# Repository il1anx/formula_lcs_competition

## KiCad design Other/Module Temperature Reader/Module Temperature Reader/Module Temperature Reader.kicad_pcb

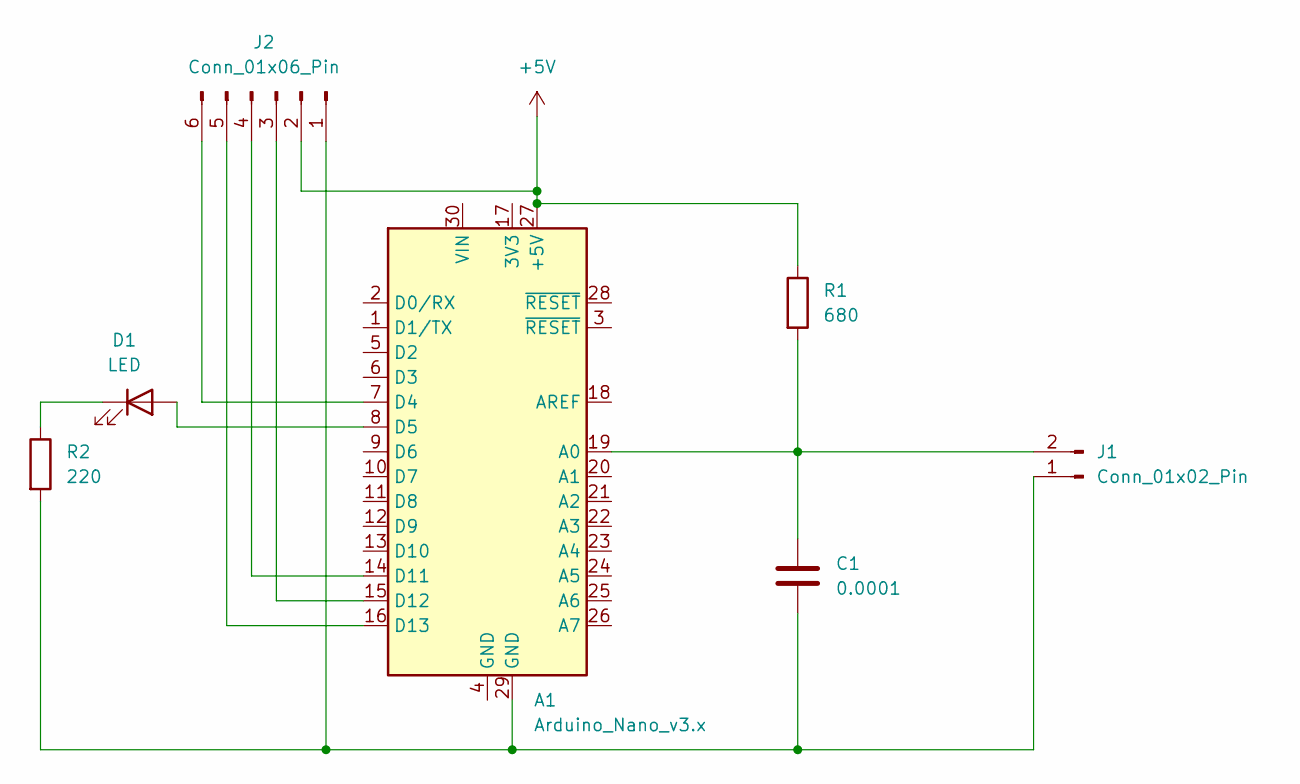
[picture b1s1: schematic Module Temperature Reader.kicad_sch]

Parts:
A1: Arduino_Nano_v3.x; Arduino_Nano
C1: 0.0001; C_1206_3216Metric
D1: LED; LED_D3.0mm
J1: Conn_01x02_Pin; JST_XH_B2B-XH-A_1x02_P2.50mm_Vertical
J2: Conn_01x06_Pin; PinSocket_1x06_P2.54mm_Vertical
R1: 680; R_1206_3216Metric
R2: 220; R_1206_3216Metric

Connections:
+5V: A1.27 (+5V), J2.2, R1.1
unnamed: A1.19 (A0), C1.1, J1.2, R1.2
unnamed: A1.7 (D4), J2.6
unnamed: A1.8 (D5), D1.2 (A)
unnamed: A1.14 (D11), J2.4
unnamed: A1.15 (D12), J2.3
unnamed: A1.16 (D13), J2.5
unnamed: D1.1 (K), R2.1
unnamed: A1.29 (GND), C1.2, J1.1, J2.1, R2.2

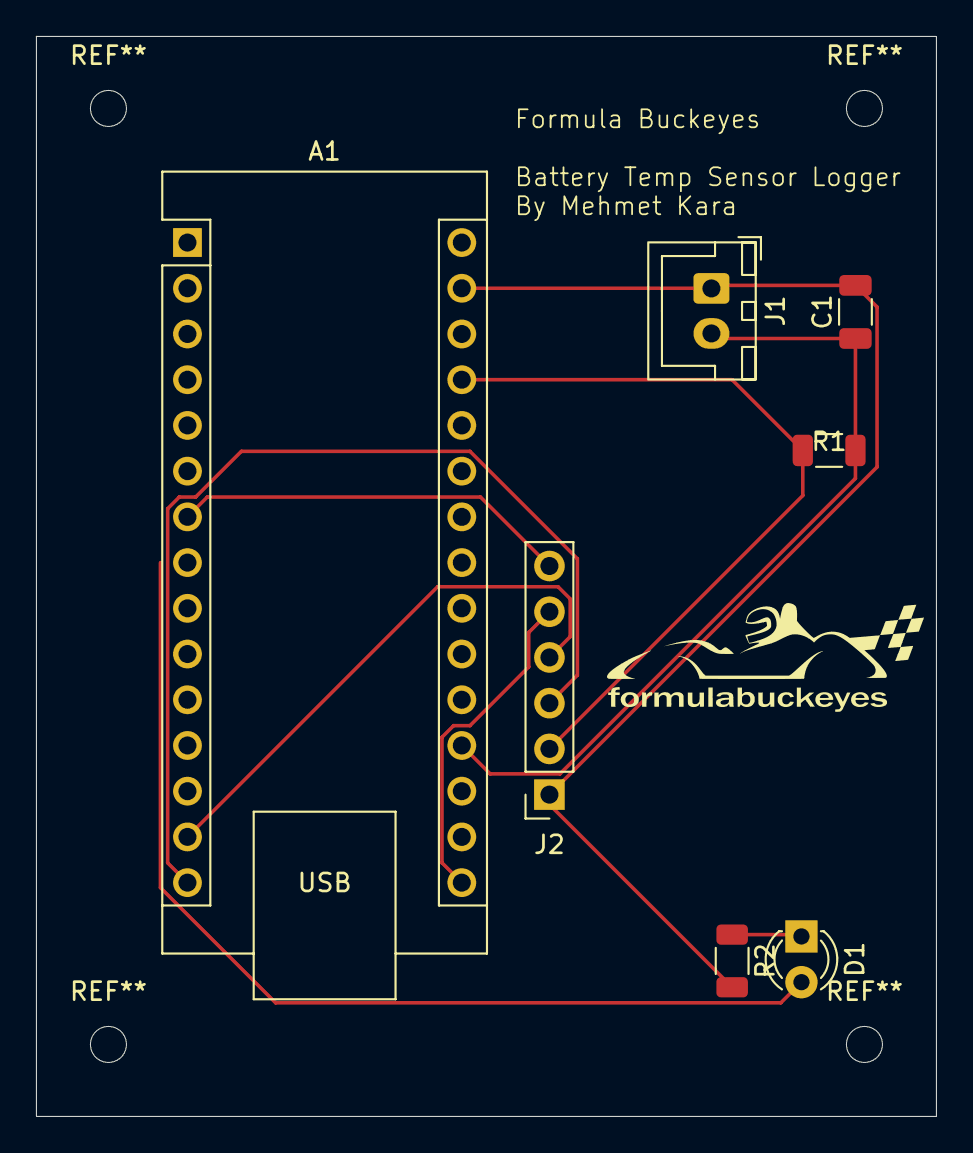
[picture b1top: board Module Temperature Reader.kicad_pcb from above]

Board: 2 copper layers, 50.0 x 60.0 mm, 7 parts (0 on the bottom side), 9 nets.

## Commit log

2025-08-05 Adding the regen braking mlx Stacey gave me
2025-08-29 Added MoTeC documentation
    Provided by Matthew Chang
2025-08-29 Added FB25 era files
    Staceys torque vectoring and traction control algorithms plus some regen stuff
2025-09-05 Added V1
    Contains two simulink files to initially test the m150 simulink tools with. One with a variable, one without.
2025-09-06 Added PID tuning folder
    PID tuning will be done in CarSim with modified copies of V0
2025-09-24 Lump cell battery modeling w/ DD
2025-09-29 9/29/2025 update
2025-09-29 Added Enapaq cell data sheets
2025-09-29 Single cell tester with updated v6 values
2025-09-29 added 24b version
2025-09-29 Created fbuildv0.1
    First iteration of the controls meant to be written to the m150.
2025-09-30 Standardized variable names added to v0.1
    Variable name list and notes are in the v0_signal_names xlsx
2025-09-30 V0.1 with variables contained within the model workspace
    PID tables still need adjusting for TV!
2025-09-30 V0.1 with updated TV PID controller gain tables
2025-09-30 V0.2 added
    Gets rid of outputs that arent relevant for the actual vehicle, as well as some blocks such as the understeer gradient calculator.
2025-10-01 cfirmv0p3 added + file reorg
2025-10-01 cbuildv0p4 added
    Updated yaw rate target estimation and fixed carsim sensor units.
2025-10-02 cbuildv0p4 added
    Improved yaw rate target and vehicle velocity calculations.
2025-10-06 Added Architecture 1.0
2025-10-06 Fixing broken push
2025-10-08 Architecture Updates
2025-10-08 added V1 tv folder
2025-10-20 1ms step time update
2025-10-20 Updated current profile
2025-10-21 10-20-2025 push
2025-10-21 Created cfirmv0p1
2025-10-22 Working cbuildv1p0 and acceleration testing results
    Tested different TC settings and their impact on acceleration times.
2025-10-22 Updated cfirmv1p0 with from and goto blocks
2025-10-22 Slack push notification test
2025-10-22 Organization and dashboard creation
2025-10-23 TC Tuning script
    Using updated V4 tire model.
2025-10-24 10-23-2025
2025-10-24 Fixed Tmax allocation
2025-10-28 Fixed DDR velocity dependence
2025-10-28 V1 variable list updated
2025-10-30 Battery model updates
2025-10-31 Current profile v1 data and analysis uploaded
2025-11-02 Lump Cell V8 uploaded
    Better voltage estimation.
2025-11-04 Updated V8 voltage estimation + FMEA`
2025-11-05 DiL V1.0
2025-11-06 DiL V1.0 Updates
2025-11-09 cfirm v1.1
    Has yaw rate estimation and error
2025-11-09 20 deg sin steer analysis for v1.1
2025-11-11 Enapaq module data sheet added
2025-11-11 Temperature sensor LUT added
2025-11-13 V2.0 created
2025-11-14 Sin steer analysis plotter added
2025-11-16 V8 voltage plotting comparison
2025-11-17 V2 and V1 controls analysis + V8 lump cell analysis
2025-11-19 DiL V2 created
2025-11-28 Controls v2.1
    Has low speed tv protection
2025-11-30 Added fs energy deployment paper
2025-12-01 V2.1 DiL updates + -0.25 run data
2025-12-02 DiL V2.1 updates
2025-12-02 DiL V3.0 created
    improved TC with p-controller
2025-12-02 Corrections to V2.1
2025-12-02 Updated V2.1 gear ratio
    Switched to 13.75 to reflect changes to FB26 gearbox design.
2025-12-02 More V2.1 updates
2025-12-02 Swapped DiL controllers to 2024b
    From 2025a
2025-12-02 Swapped V3.0 to 2024b
2025-12-05 Butterworth CPU benchmark script
2025-12-05 6C-2B-59-DC-40-27 test
2025-12-05 4C-D7-17-97-99-A6 test
2025-12-05 butterworth testing mac address dictionary
2025-12-05 2018 macbook pro testing
2025-12-05 updated mac address dictionary
2025-12-05 scott e205 run
2025-12-05 e225 testing
2025-12-05 updated p2000 compatibility
2025-12-05 tested home desktop
2025-12-07 V3.0 in carsim + tuning + battery model improvements
2025-12-07 v3.0 updates
2025-12-07 Updated V3.0 DiL battery model
2025-12-07 V3.0 DiL updates + endurance results
2025-12-07 DiL Physics PC CPU test
2025-12-13 Misc controller updates+ battery model updates
2025-12-18 Offline and DiL V3.1 uploads
    Improved slip estimation
2025-12-18 Misc updates to DiL v3.1
2026-01-11 New powertrain model uploaded
2026-01-15 Created CarSim data truncation tool
2026-01-20 Misc v3.1 updates
2026-01-21 Updated battery module temp reader
2026-01-21 Current profile for v2 module test
2026-01-21 Added truncated carsim data
2026-01-21 Created LUT for module temperature sensor
2026-01-23 Adiabatic round 2 module test data + photos
2026-01-25 Module Testing Round 2 adiabatic test plots
2026-01-27 Demo for todays lecture
2026-01-28 Round 2 RCID test data and round 2 ambient test data
2026-01-29 Updated battery model to simulate enapaq sensor
2026-02-04 Ambient test graphs + RCID pp script
2026-02-05 TSAC fuse data sheet added
2026-02-05 Full RCID post processing folder from Faissal uploaded
2026-02-11 Added current detection function to RCID tool folder
2026-02-11 VTC6 round 2 rcid test 25 deg C results uploaded
    1 RC branch
2026-02-11 Sony VTC6 Round 2 RCID 40 degrees results uploaded
    1 rc branch
2026-02-11 Changes to the post processing script uploaded
    Fixed how it loads rcid raw data
2026-02-11 Sony VTC6 round 2 rcid 60 degrees celcius results uploaded
    1 rc branch
2026-02-18 DiL V3.2 Build Uploaded
    Redacted unneeded functions in the TC controller
2026-02-18 Created an initial simulink model for motec firmware
2026-02-18 Round 2 RCID test extra plots uploaded
2026-02-18 updated firmware v3.2 variables
2026-02-18 Corrections to fbuild v3.2
    Removed ghost goto and from blocks
2026-02-18 Additional changes to fbuild v3.2
2026-02-18 Changed DiL control model block containment structure
2026-02-18 V9 Battery Model Created
2026-02-18 Tabulated cell data from rcid test 2
2026-02-18 More V9 updates
2026-02-19 Adjusted RC model
2026-03-22 initial commit: V1 and V2
2026-03-22 fix V2
2026-03-22 add V3
